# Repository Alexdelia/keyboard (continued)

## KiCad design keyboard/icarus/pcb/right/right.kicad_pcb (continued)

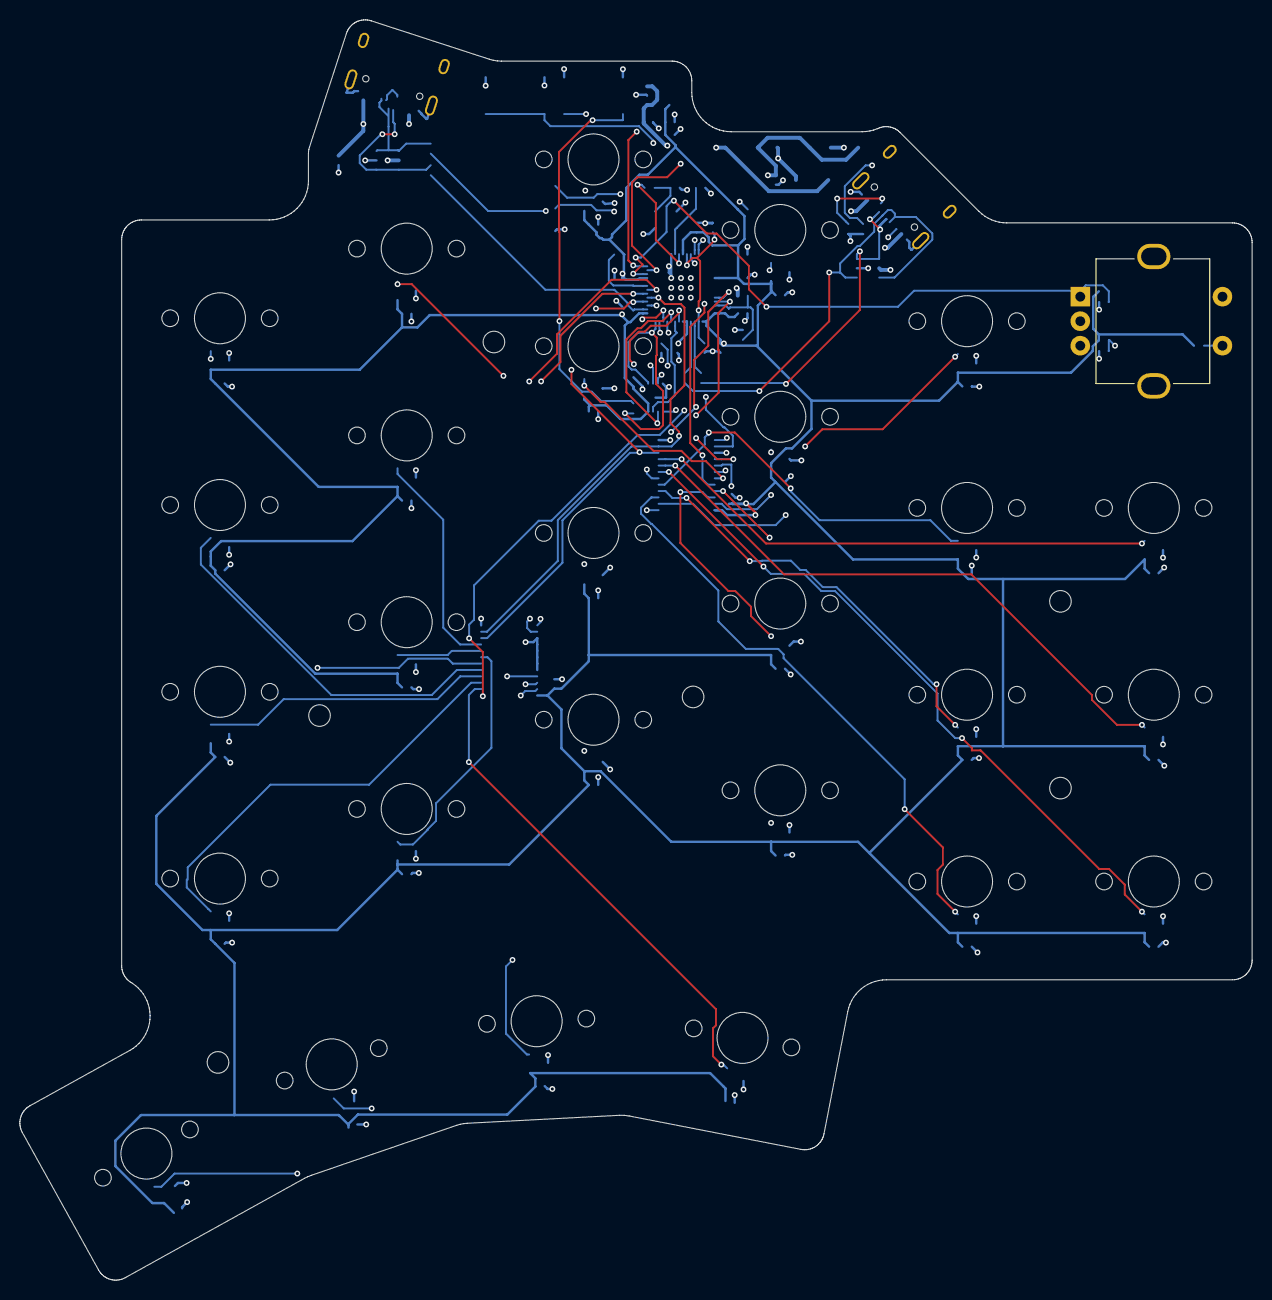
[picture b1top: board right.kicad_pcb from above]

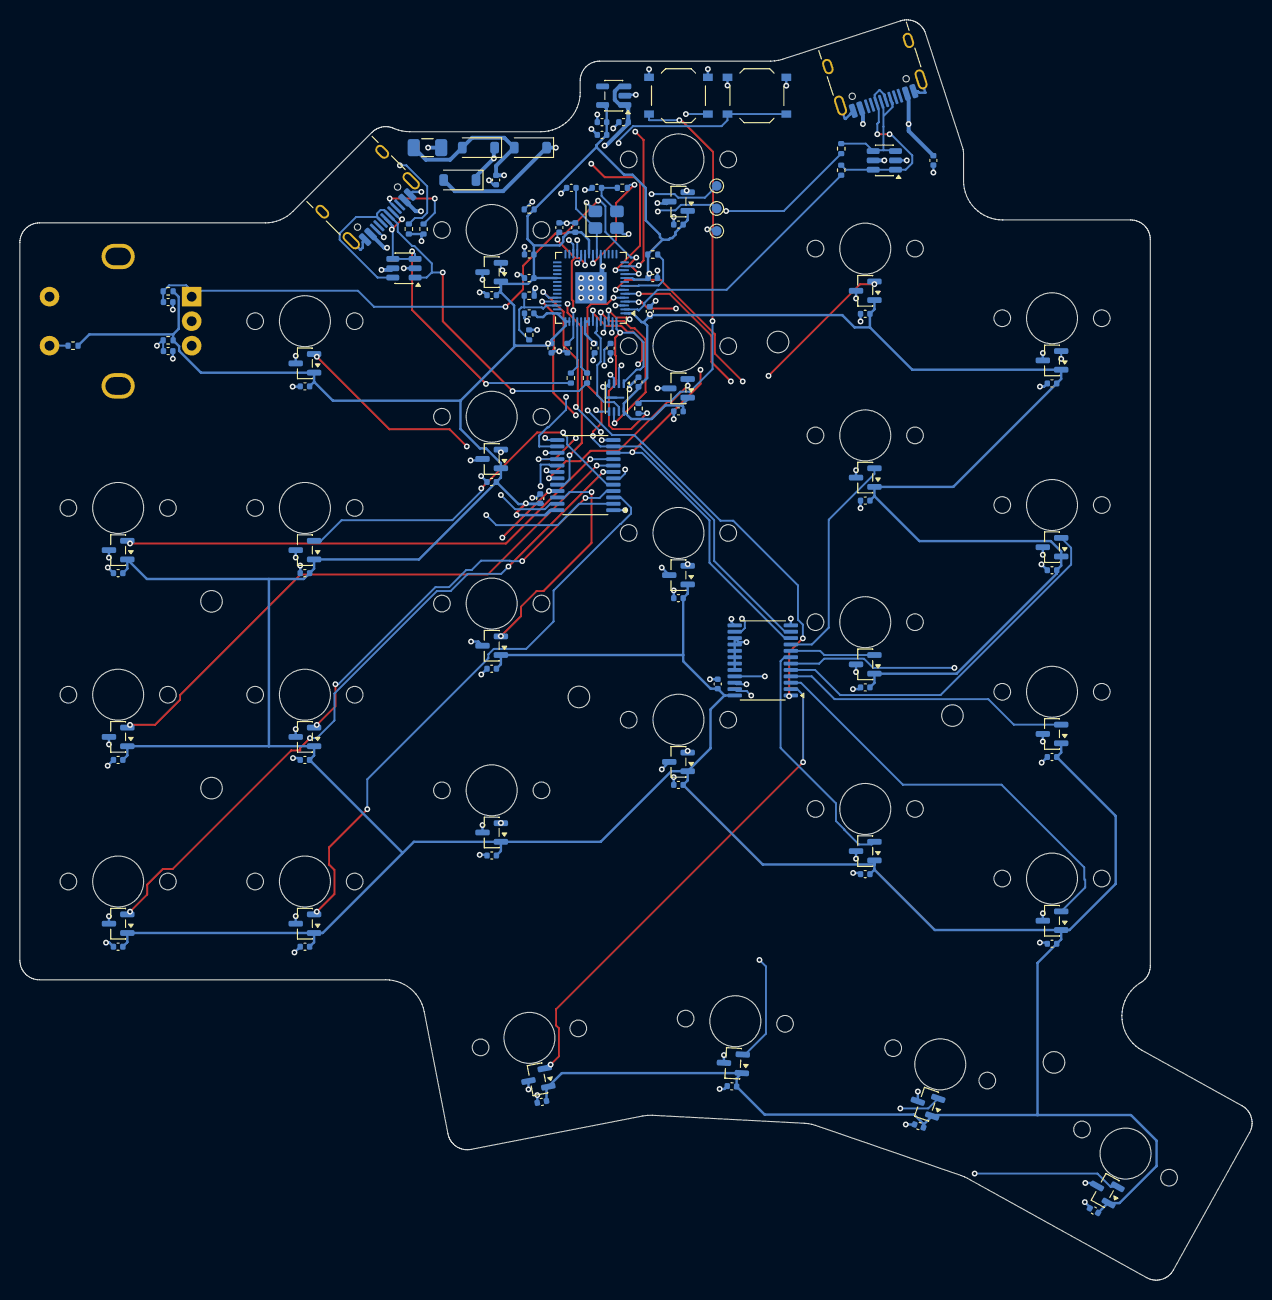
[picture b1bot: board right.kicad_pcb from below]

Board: 4 copper layers, 125.7 x 128.5 mm, 145 parts (111 on the bottom side), 68 nets.

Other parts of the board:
K1: top-pinkyOuter; Gateron_KS33_Magnetic_Jade
K2: home-pinkyOuter; Gateron_KS33_Magnetic_Jade
K3: bottom-pinkyOuter; Gateron_KS33_Magnetic_Jade
K4: number-pinky; Gateron_KS33_Magnetic_Jade
K5: top-pinky; Gateron_KS33_Magnetic_Jade
K6: home-pinky; Gateron_KS33_Magnetic_Jade
K7: bottom-pinky; Gateron_KS33_Magnetic_Jade
K8: number-ring; Gateron_KS33_Magnetic_Jade
K9: top-ring; Gateron_KS33_Magnetic_Jade
K10: home-ring; Gateron_KS33_Magnetic_Jade
K11: bottom-ring; Gateron_KS33_Magnetic_Jade
K12: number-middle; Gateron_KS33_Magnetic_Jade
K13: top-middle; Gateron_KS33_Magnetic_Jade
K14: home-middle; Gateron_KS33_Magnetic_Jade
K15: bottom-middle; Gateron_KS33_Magnetic_Jade
K16: number-index; Gateron_KS33_Magnetic_Jade
K17: top-index; Gateron_KS33_Magnetic_Jade
K18: home-index; Gateron_KS33_Magnetic_Jade
K19: bottom-index; Gateron_KS33_Magnetic_Jade
K20: number-indexInner; Gateron_KS33_Magnetic_Jade
K21: top-indexInner; Gateron_KS33_Magnetic_Jade
K22: home-indexInner; Gateron_KS33_Magnetic_Jade
K23: bottom-indexInner; Gateron_KS33_Magnetic_Jade
K24: thumb0; Gateron_KS33_Magnetic_Jade
K25: thumb1; Gateron_KS33_Magnetic_Jade
K26: thumb2; Gateron_KS33_Magnetic_Jade
K27: thumb3; Gateron_KS33_Magnetic_Jade
MH1, MH2, MH3, MH4, MH5, MH6: M2; MountingHole_2.2mm_M2

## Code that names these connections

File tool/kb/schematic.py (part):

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MUX_SELECT_GPIOS = [2, 3, 4, 5]
ADC_GPIOS = [26, 27]
ENCODER_GPIOS = {"a": 8, "b": 9, "push": 10}
LINK_DP_GPIO = 0
LINK_DM_GPIO = 1
HOST_VBUS_SENSE_GPIO = 28
HANDEDNESS_GPIO = 6
GPIO: dict[str, int | list[int] | dict[str, int]] = {
	"muxSelect": MUX_SELECT_GPIOS,
	"adc": ADC_GPIOS,
	"encoder": ENCODER_GPIOS,
	"linkDp": LINK_DP_GPIO,
	"linkDm": LINK_DM_GPIO,
	"hostVbusSense": HOST_VBUS_SENSE_GPIO,
	"handedness": HANDEDNESS_GPIO,
}
ENCODER_NETS = {"a": "ENC_A", "b": "ENC_B", "push": "ENC_SW"}
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
def gpio_nets() -> dict[int, str]:
	nets = {
		LINK_DP_GPIO: "LINK_DP",
		LINK_DM_GPIO: "LINK_DM",
		HOST_VBUS_SENSE_GPIO: "HOST_VBUS_SENSE",
		HANDEDNESS_GPIO: "HAND",
	}
	nets.update({gpio: select_net(i) for i, gpio in enumerate(MUX_SELECT_GPIOS)})
	nets.update({gpio: com_net(i) for i, gpio in enumerate(ADC_GPIOS)})
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				"LINK_VBUS", (None, None), "LINK_DP_CONN", "LINK_DM_CONN"
			),
		),
		c.two_pin("fuse", "F1", "HOST_VBUS_RAW", "HOST_VBUS"),
		c.diode("D1", anode="HOST_VBUS", cathode="+5V"),
		c.diode("D2", anode="LINK_VBUS", cathode="+5V"),
		c.diode("D3", anode="HOST_VBUS", cathode="LINK_VBUS"),
		c.two_pin("button", "SW1", "BOOT", "GND"),
		c.two_pin("button", "SW2", "RUN", "GND"),
		c.two_pin("res_5k1_0402", "R1", "HOST_CC1", "GND"),
		c.two_pin("res_5k1_0402", "R2", "HOST_CC2", "GND"),
		c.two_pin("res_27r_0402", "R3", "USB_DP_CONN", "USB_DP"),
		c.two_pin("res_27r_0402", "R4", "USB_DM_CONN", "USB_DM"),
		c.two_pin("res_1k_0402", "R5", "LINK_DP_CONN", "LINK_DP"),
		c.two_pin("res_1k_0402", "R6", "LINK_DM_CONN", "LINK_DM"),
		c.two_pin("res_1k_0402", "R7", "XOUT", "XTAL_OUT"),
		c.two_pin("res_1k_0402", "R8", "QSPI_SS", "BOOT"),
		c.two_pin("res_10k_0402", "R9", "+3V3", "RUN"),
		c.two_pin("res_2k2_0402", "R10", "HOST_VBUS", "HOST_VBUS_SENSE"),
		c.two_pin("res_3k3_0402", "R11", "HOST_VBUS_SENSE", "GND"),
		c.two_pin("cap_4u7_0402", "C1", "+5V", "GND"),
		c.two_pin("cap_10u_0402", "C2", "+3V3", "GND"),
		c.two_pin("cap_1u_0402", "C3", "+3V3", "GND"),
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		c.two_pin("cap_100n_0402", "C12", "+1V1", "GND"),
		c.two_pin("cap_100n_0402", "C16", "+3V3", "GND"),
		c.two_pin("cap_100n_0402", "C21", "+3V3", "GND"),
		c.two_pin("cap_15p_0402", "C17", "XIN", "GND"),
		c.two_pin("cap_15p_0402", "C18", "XTAL_OUT", "GND"),
		c.two_pin("cap_100n_0402", "C19", "HOST_VBUS", "GND"),
		c.two_pin("cap_100n_0402", "C20", "LINK_VBUS", "GND"),
		test_point("TP1", "SWCLK"),
		test_point("TP2", "SWDIO"),
		test_point("TP3", "GND"),
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			c.part("sensor", sensor, {"1": "+3V3", "2": output, "3": "GND"}, KEY=key)
		)
		parts.append(c.two_pin("cap_100n_0402", cap, "+3V3", "GND"))
	parts.append(c.two_pin("res_10k_0402", "R101", "HAND", STRAP_RAIL[side]))
	for key, encoder in encoder_refs(side).items():
		parts.append(
			c.part(
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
